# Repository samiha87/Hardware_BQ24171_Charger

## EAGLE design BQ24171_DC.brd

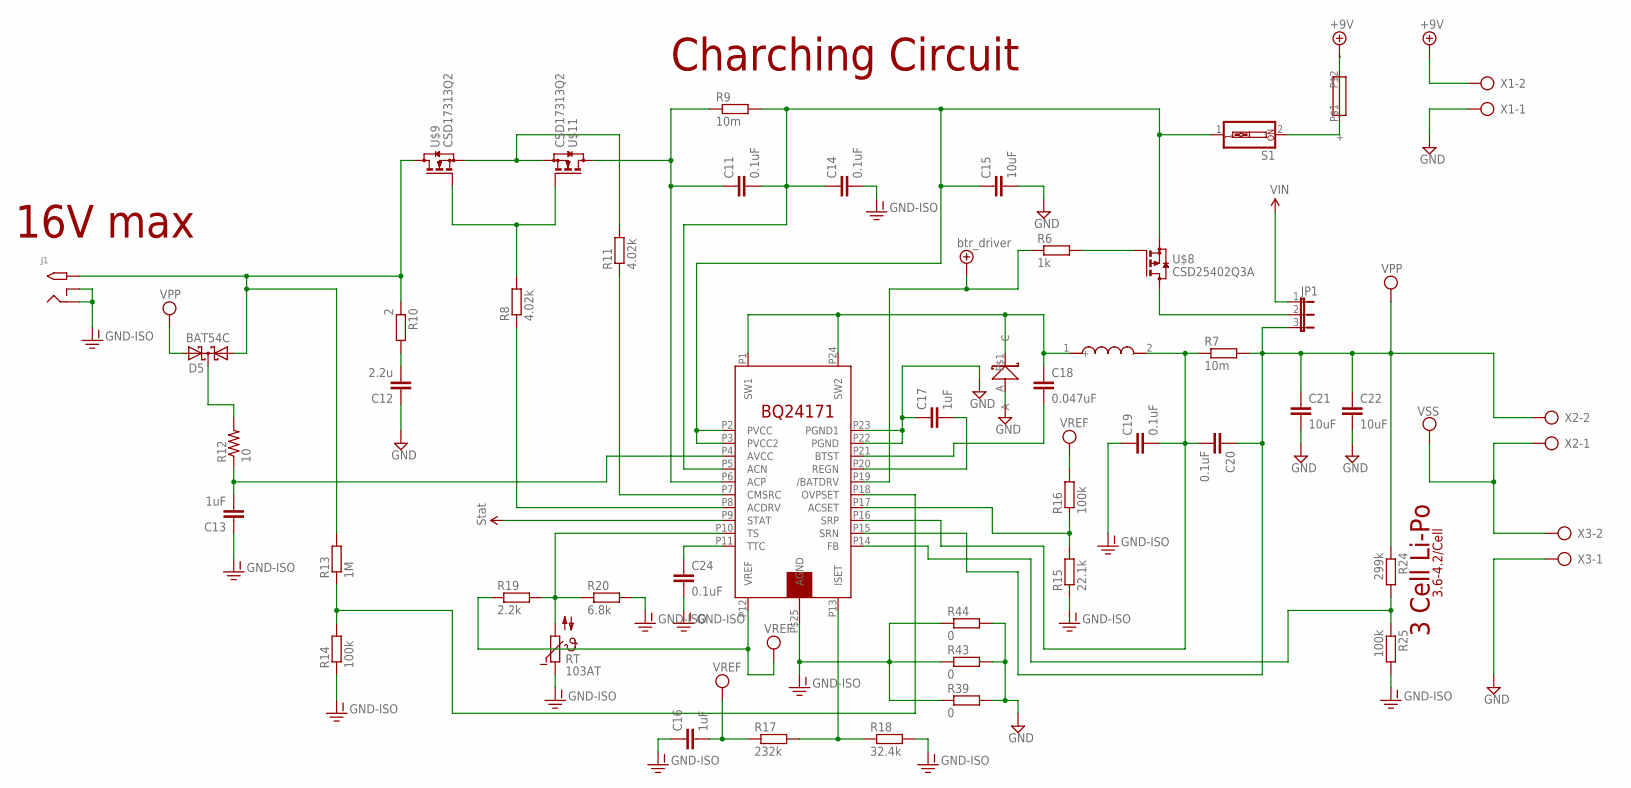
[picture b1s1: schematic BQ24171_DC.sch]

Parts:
B220-1: B220; SMA
C11, C14, C19, C20, C24: 0.1uF; C1206
C12: 2.2u; C1206
C13, C16, C17: 1uF; C1206
C15, C21, C22: 10uF; C1206
C18: 0.047uF; C1206
D5: BAT54C; SOT23
J1: 2.1MMJACKTHM; PJ-102A
JP1: JP2E; JP2
R6: 1k; M1206
R7, R9: 10m; R1206
R8, R11: 4.02k; R1206
R10: 2; R1206
R12: 10; R1206
R13: 1M; R1206
R14, R25: 100k; R1206
R15: 22.1k; R1206
R16: 100k; M1206
R17: 232k; R1206
R18: 32.4k; M1206
R19: 2.2k; R1206
R20: 6.8k; R1206
R24: 299k; R1206
R39, R43, R44: 0; R1206
RT: 103AT; P640
S1: SW_DIP-1; EDG-01
U$5: BQ24171; VQFN-N24
U$7: 3.3uH; IHLP-202CZ-01
U$8: CSD25402Q3A; Q3A
U$9, U$11: CSD17313Q2; Q2
U$17: FUSE; 1808
X1, X2, X3: AK300/2

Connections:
1.0V: U$5.P9 (STAT)
+9V: U$17.P$2 (-), X1.2
+UB: R6.1, U$5.P19 (/BATDRV)
AVCC: C13.2, R12.1, U$5.P4 (AVCC)
BTST: C18.2, U$5.P21 (BTST)
FB: R24.2, R25.1, U$5.P14 (FB)
GND: B220-1.A, C12.1, C15.2, C17.1, C21.2, C22.2, R39.2, R43.2, R44.2, U$5.P22 (PGND), U$5.P23 (PGND1), X1.1, X3.1
GND-ISO: C13.1, C14.2, C16.1, C19.1, C24.2, J1.RING, J1.RING_SW, R14.1, R15.1, R18.2, R20.2, R25.2, R39.1, R43.1, R44.1, RT.1, U$5.P$25 (AGND)
ISET: R17.2, R18.1, U$5.P13 (ISET)
unnamed: JP1.2, U$8.1 (D), U$8.2 (D), U$8.3 (D)
unnamed: D5.1 (A1), J1.TIP, R10.1, R13.2, U$9.1 (D), U$9.2 (D), U$9.5 (D), U$9.6 (D), U$9.8 (D)
unnamed: R15.2, R16.1, U$5.P17 (ACSET)
unnamed: C11.2, C14.1, C15.1, R9.2, S1.1, U$5.P2 (PVCC), U$5.P3 (PVCC2), U$5.P5 (ACN), U$8.5 (S), U$8.6 (S), U$8.7 (S), U$8.8 (S), U$8.P$5 (S)
unnamed: R6.2, U$8.4 (G)
unnamed: B220-1.P$1 (C), C18.1, U$5.P1 (SW1), U$5.P24 (SW2), U$7.1 (+)
unnamed: C19.2, C20.2, R7.1, U$5.P16 (SRP), U$7.2 (-)
unnamed: R8.2, U$9.3 (G), U$11.3 (G)
unnamed: R8.1, U$5.P8 (ACDRV)
unnamed: R11.2, U$9.4 (S), U$9.7 (S), U$11.4 (S), U$11.7 (S)
unnamed: C11.1, R9.1, U$5.P6 (ACP), U$11.1 (D), U$11.2 (D), U$11.5 (D), U$11.6 (D), U$11.8 (D)
unnamed: C12.2, R10.2
unnamed: R11.1, U$5.P7 (CMSRC)
unnamed: R19.2, R20.1, RT.2, U$5.P10 (TS)
unnamed: R13.1, R14.2, U$5.P18 (OVPSET)
unnamed: D5.3 (CC), R12.2
unnamed: S1.2, U$17.P$1 (+)
REGN: C17.2, U$5.P20 (REGN)
TTC: C24.1, U$5.P11 (TTC)
VEE: C16.2, R16.2, R17.1, R19.1, U$5.P12 (VREF)
VIN: JP1.1
VPP: C20.1, C21.1, C22.1, D5.2 (A2), JP1.3, R7.2, R24.1, U$5.P15 (SRN), X2.2
VSS: X2.1, X3.2

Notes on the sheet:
3 Cell Li-Po
3.6-4.2/Cell
Charching Circuit
16V max

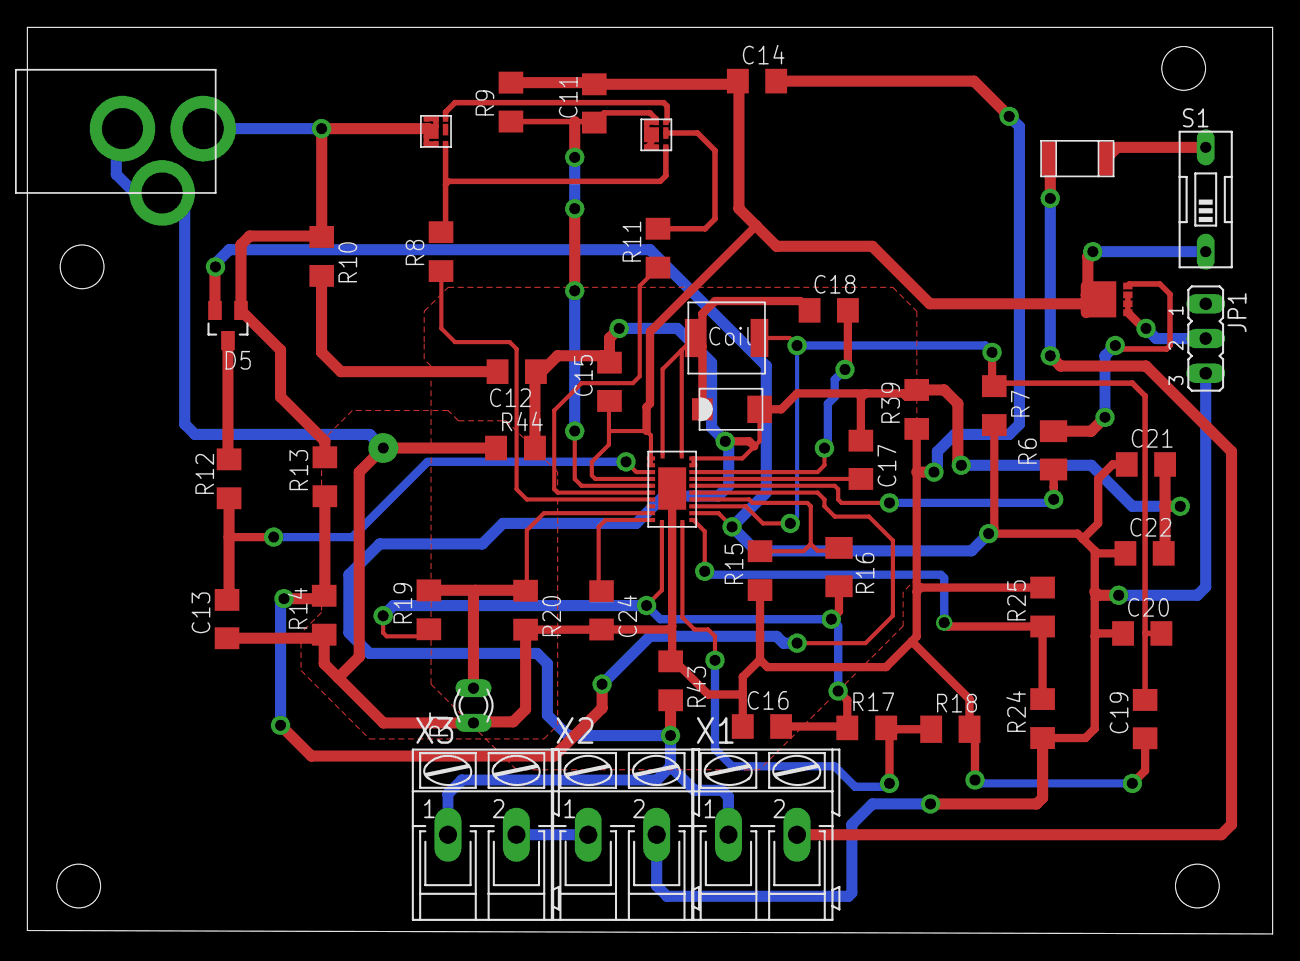
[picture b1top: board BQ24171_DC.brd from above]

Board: 2 copper layers, 91.0 x 66.2 mm, 48 parts (1 on the bottom side), 30 nets.

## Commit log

2019-08-24 BQ24171 brakout board

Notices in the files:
parts and their libraries:
SparkFun-Aesthetics: Licensing: Creative Commons ShareAlike 4.0 International - https://creativecommons.org/licenses/by-sa/4.0
